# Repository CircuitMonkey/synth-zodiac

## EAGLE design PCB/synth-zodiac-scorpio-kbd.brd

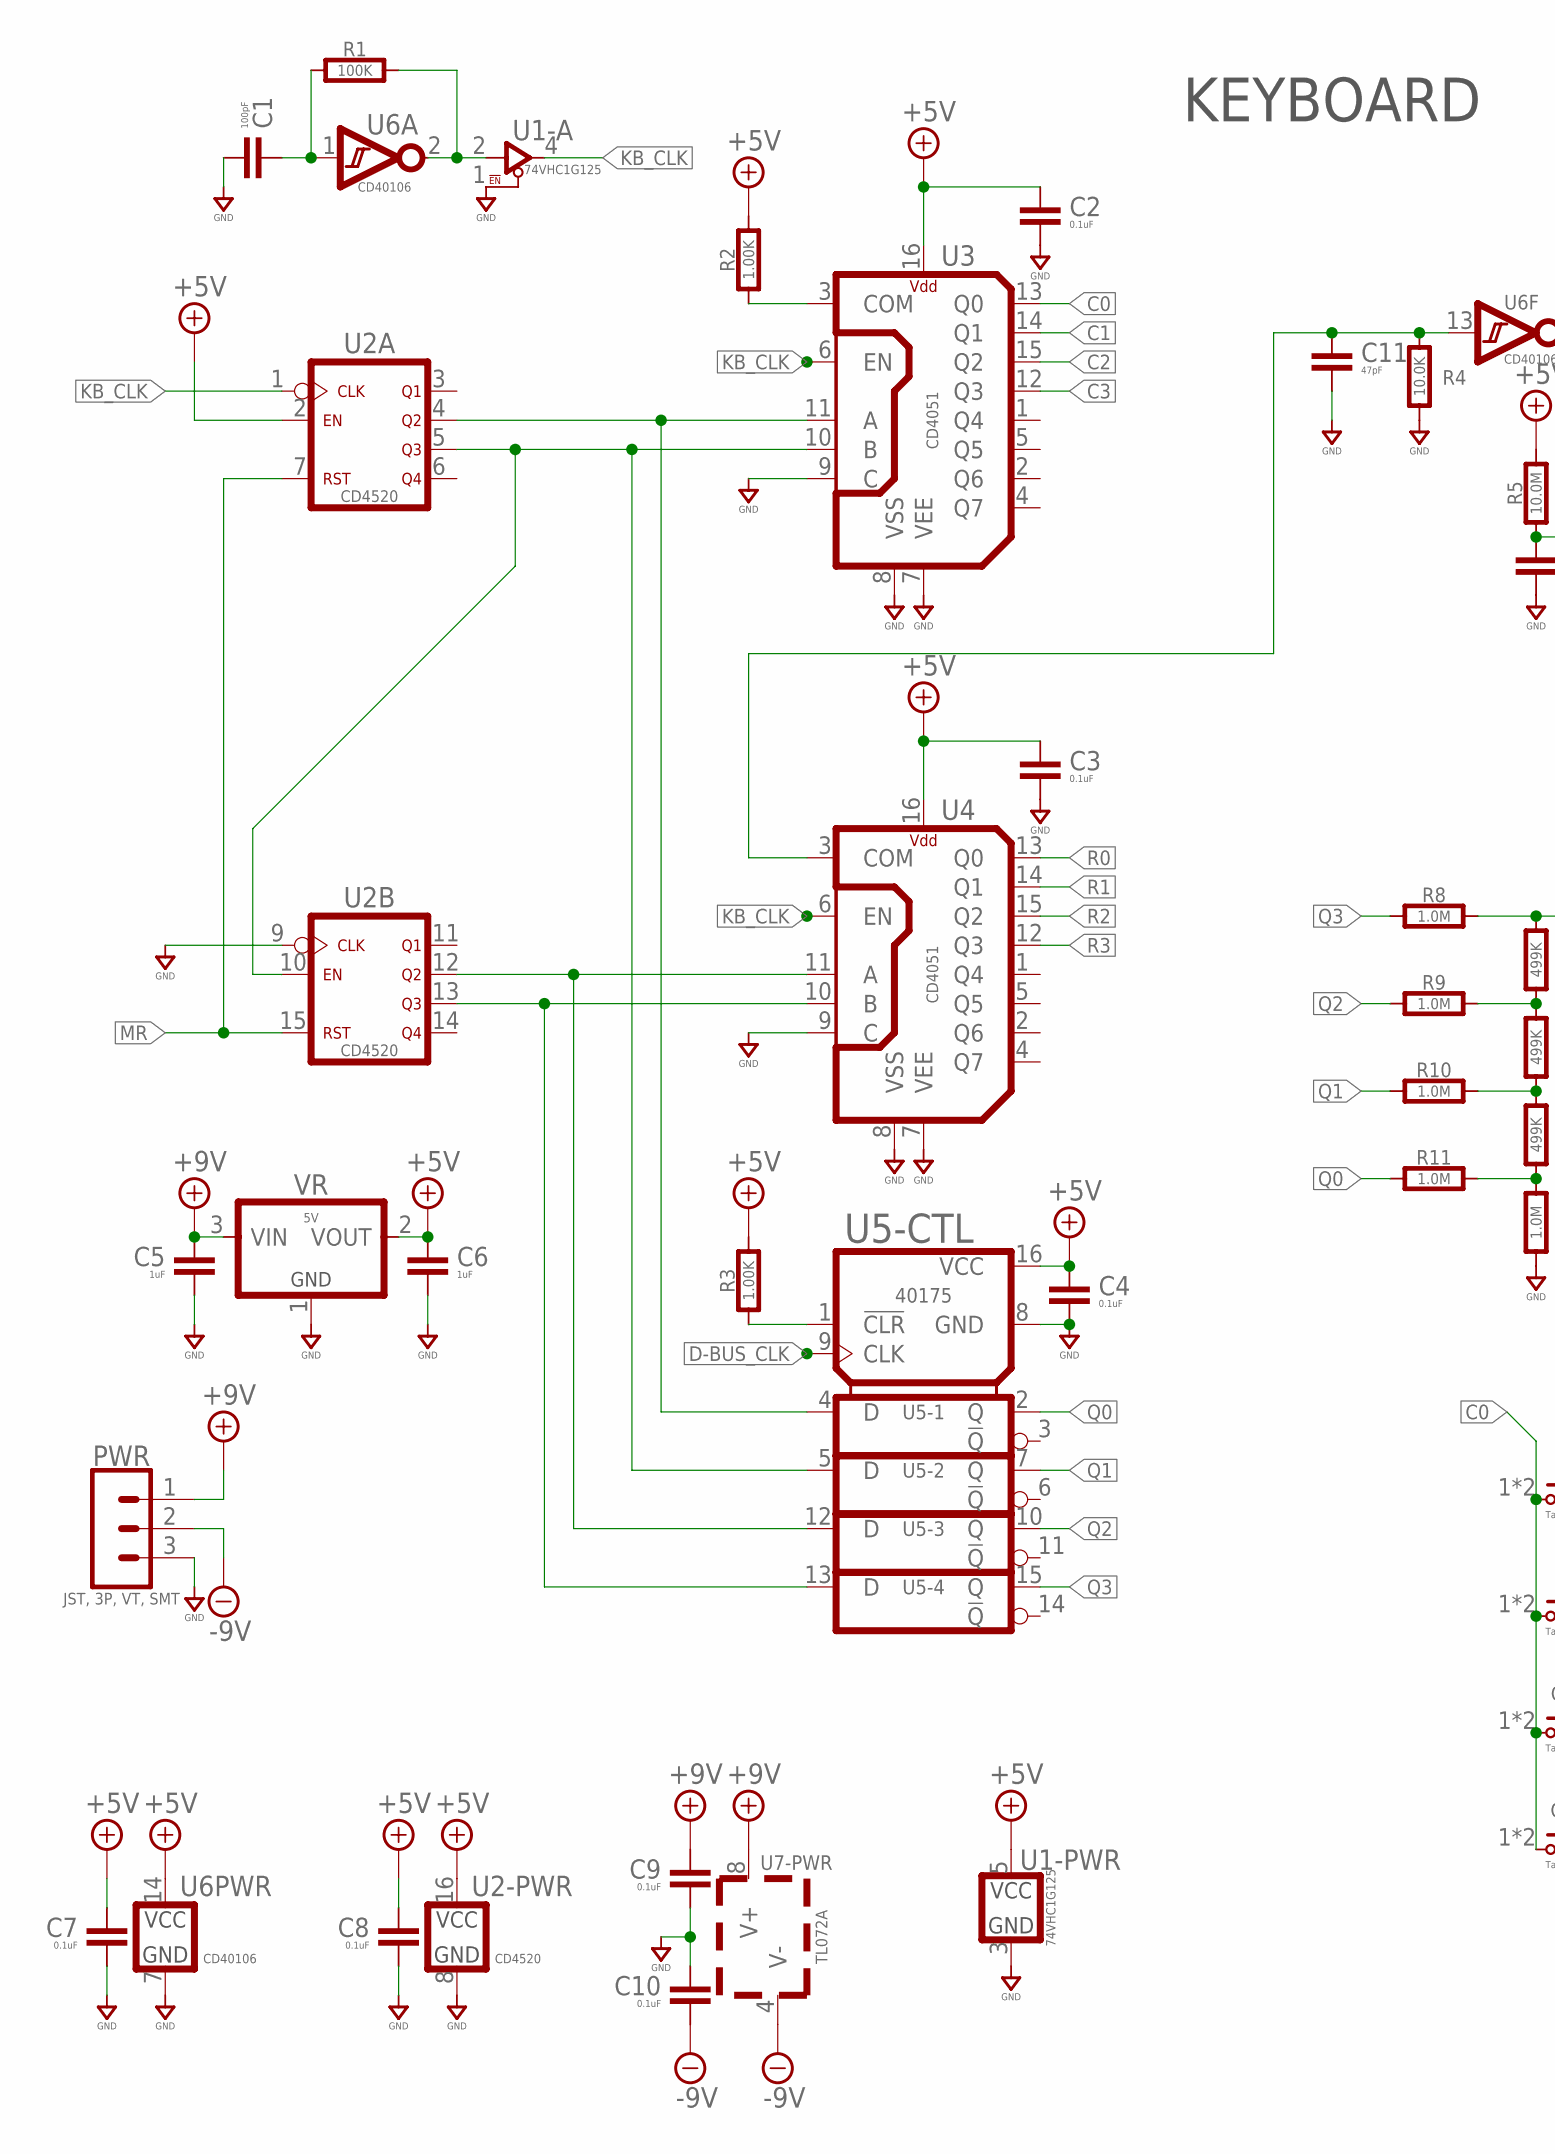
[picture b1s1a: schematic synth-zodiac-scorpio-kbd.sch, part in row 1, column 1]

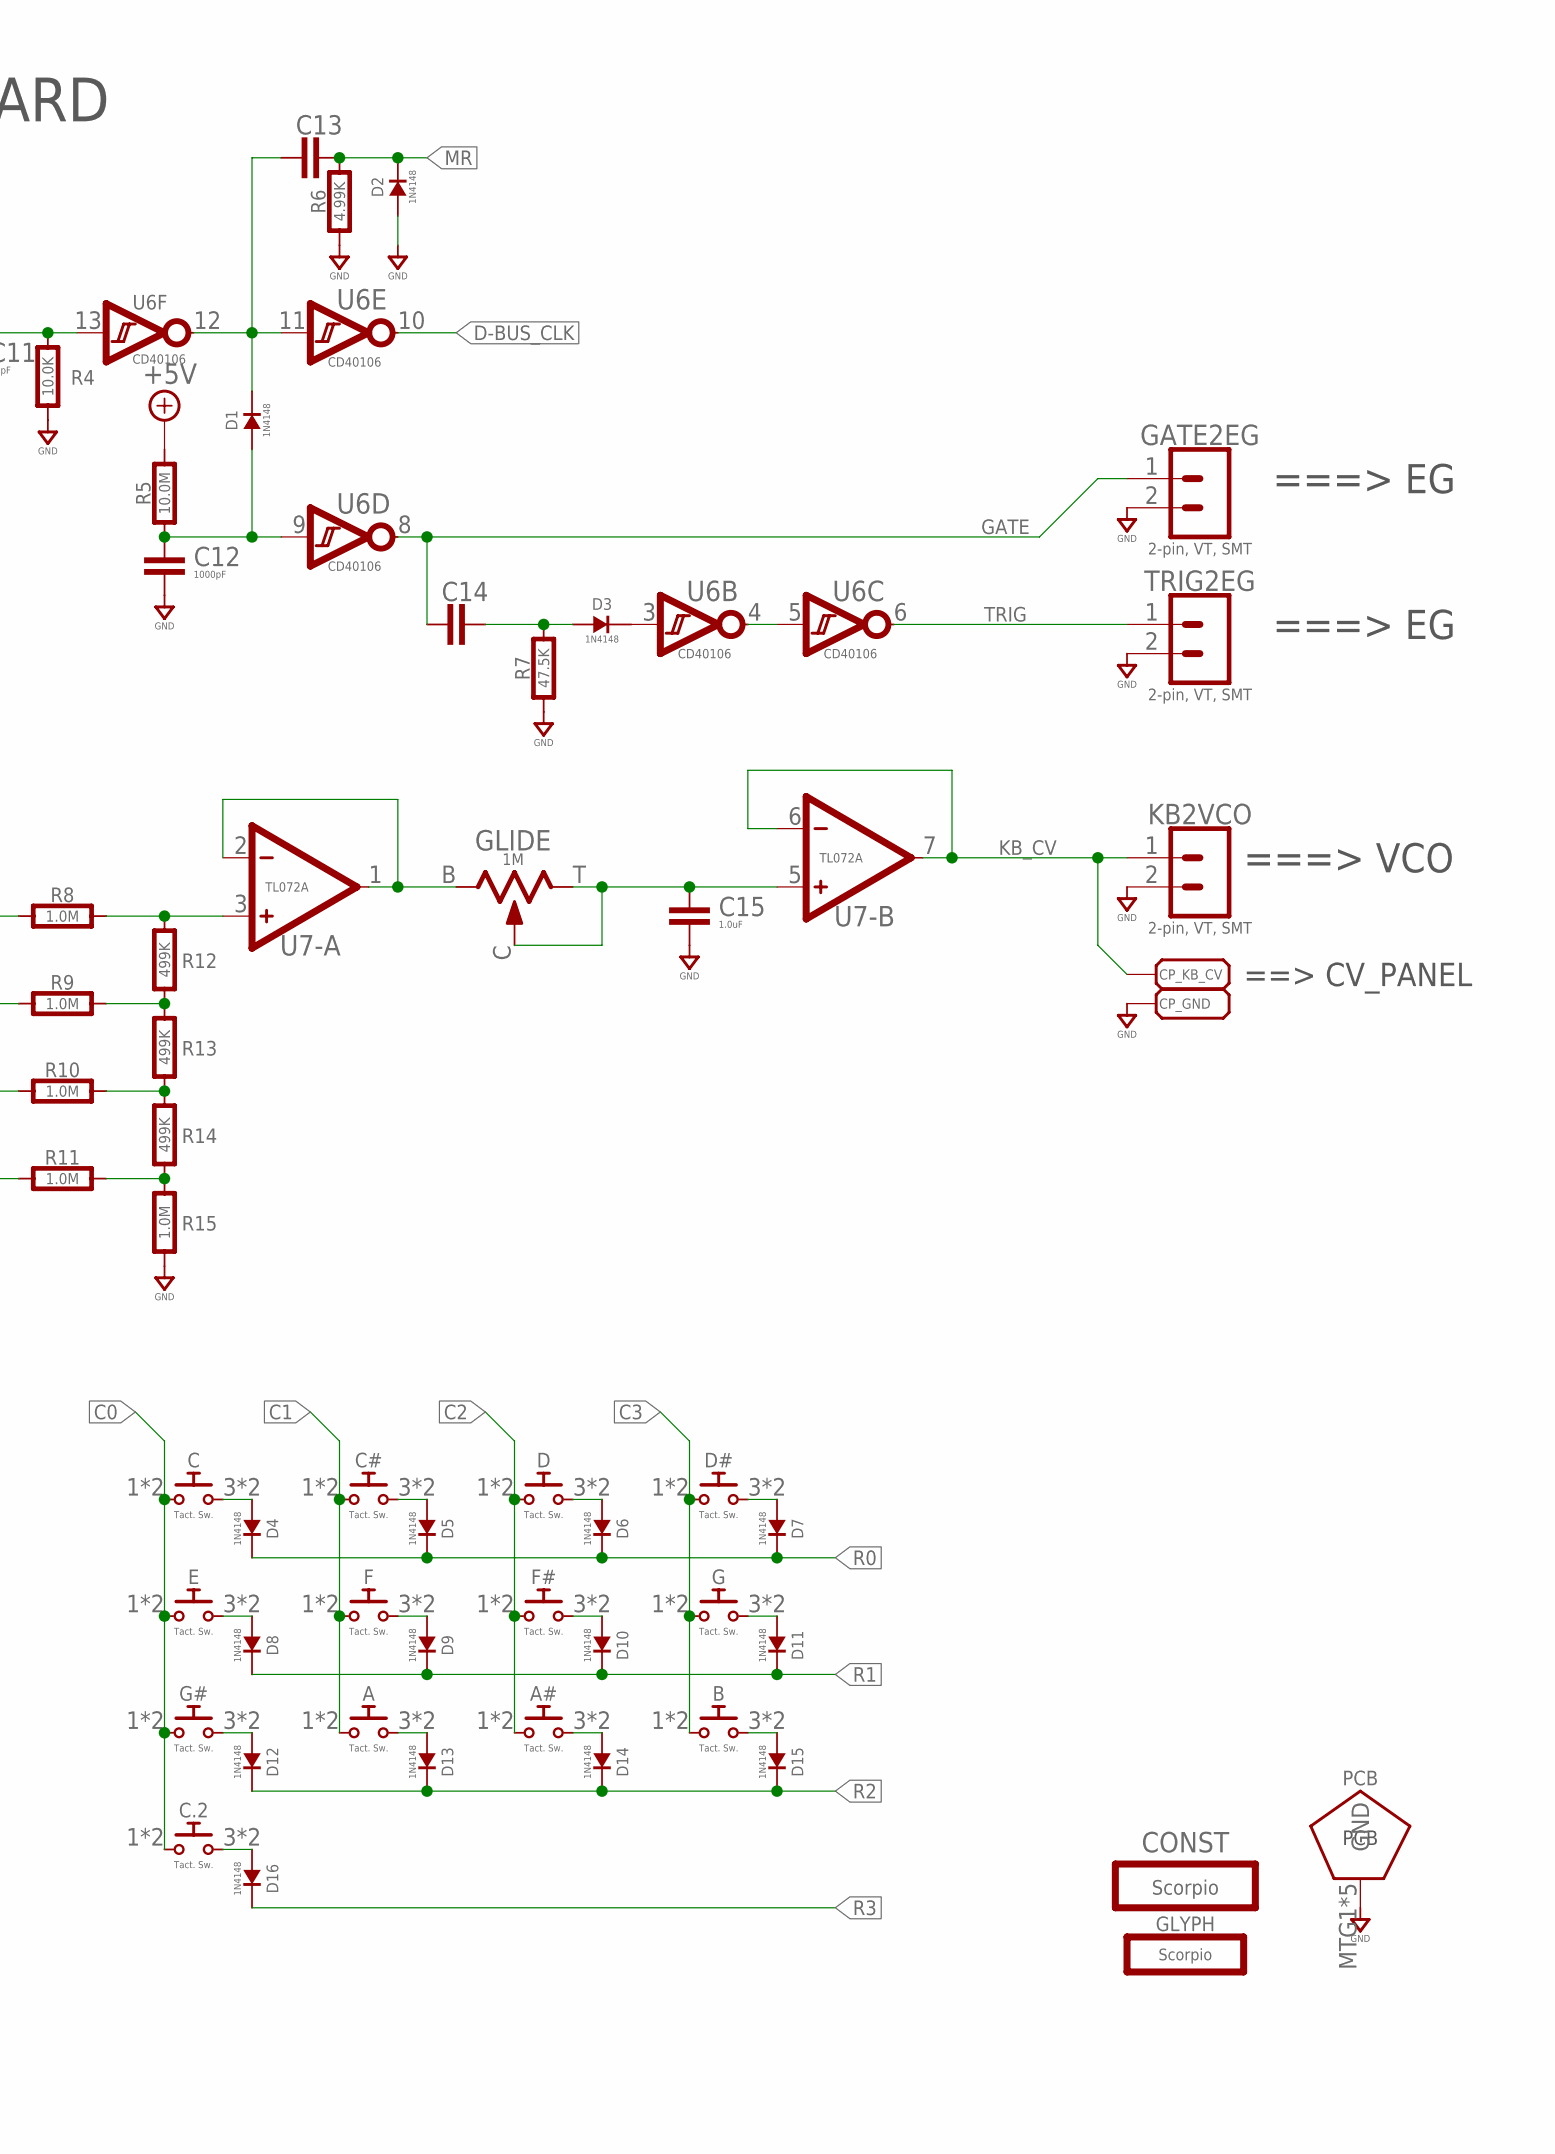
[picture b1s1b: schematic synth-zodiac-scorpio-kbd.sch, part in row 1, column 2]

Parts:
A: Tact. Sw.; B3FS
A#: Tact. Sw.; B3FS
B: Tact. Sw.; B3FS
C, C.2: Tact. Sw.; B3FS
C1: 100pF; 0603-CAP
C2, C3, C4, C7, C8, C9, C10, C14: 0.1uF; 0603-CAP
C5, C6: 1uF; 0603-CAP
C11: 47pF; 0603-CAP
C12: 1000pF; 0603-CAP
C13: 220pF; 0603-CAP
C15: 1.0uF; 0603-CAP
C#: Tact. Sw.; B3FS
CONST: Scorpio; SCORPIO-CONST
CP_GND: PAD-70X70SMD-070X070; SMD-070MIL
CP_KB_CV: PAD-70X70SMD-070X070; SMD-070MIL
D: Tact. Sw.; B3FS
D1, D2, D3, D4, D5, D6, D7, D8, D9, D10, D11, D12, D13, D14, D15, D16: 1N4148; SOD-123
D#: Tact. Sw.; B3FS
E: Tact. Sw.; B3FS
F: Tact. Sw.; B3FS
F#: Tact. Sw.; B3FS
G: Tact. Sw.; B3FS
G#: Tact. Sw.; B3FS
GATE2EG: 2-pin, VT, SMT; B2B-PH-SM4
GLIDE: 1M; POT-RV9110
GLYPH: Scorpio; SCORPIO-GLYPH
KB2VCO: 2-pin, VT, SMT; B2B-PH-SM4
PCB: PCB FAB; PENTAGON-40MM-RAD
PWR: JST, 3P, VT, SMT; B3B-PH-SM4
R1: 100K; 0603-RES
R2, R3: 1.00K; 0603-RES
R4: 10.0K; 0603-RES
R5: 10.0M; 0603-RES
R6: 4.99K; 0603-RES
R7: 47.5K; 0603-RES
R8, R9, R10, R11, R15: 1.0M; 0603-RES
R12, R13, R14: 499K; 0603-RES
TRIG2EG: 2-pin, VT, SMT; B2B-PH-SM4
U1: 74VHC1G125; TSOP-5
U2: CD4520; SO16
U3, U4: CD4051; SO16
U5: 40175; SO16
U6: CD40106; SOP14
U7: TL072A; SOP08
VR: 5V; SOT-23

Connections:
+5V: C2.1, C3.1, C4.1, C6.1, C7.1, C8.1, R2.2, R3.2, R5.2, U1.5 (VCC), U2.2 (EN), U2.16 (VCC), U3.16 (VDD), U4.16 (VDD), U5.16 (VCC), U6.14 (VCC), VR.2 (VOUT)
+9V: C5.1, C9.1, PWR.1, U7.8 (V+), VR.3 (VIN)
-9V: C10.2, PWR.2, U7.4 (V-)
C0: C.1, C.2 (1), C.2.1, C.2.2 (1), E.1, E.2 (1), G#.1, G#.2 (1), U3.13 (Q0)
C1: A.1, A.2 (1), C#.1, C#.2 (1), F.1, F.2 (1), U3.14 (Q1)
C2: A#.1, A#.2 (1), D.1, D.2 (1), F#.1, F#.2 (1), U3.15 (Q2)
C3: B.1, B.2 (1), D#.1, D#.2 (1), G.1, G.2 (1), U3.12 (Q3)
D-BUS_CLK: U5.9 (CLK), U6.10 (Y)
GATE: C14.1, GATE2EG.1, U6.8 (Y)
GND: C1.2, C2.2, C3.2, C4.2, C5.2, C6.2, C7.2, C8.2, C9.2, C10.1, C11.2, C12.2, C15.2, CP_GND.1, D2.A, GATE2EG.2, KB2VCO.2, PCB.MTG1, PCB.MTG2, PCB.MTG3, PCB.MTG4, PCB.MTG5, PWR.3, R4.1, R6.1, R7.1, R15.1, TRIG2EG.2, U1.1 (!EN), U1.3 (GND), U2.8 (GND), U2.9 (!CLK), U3.7 (VEE), U3.8 (VSS), U3.9 (C), U4.7 (VEE), U4.8 (VSS), U4.9 (C), U5.8 (GND), U6.7 (GND), VR.1 (GND)
KB_CLK: U1.4 (Y), U2.1 (!CLK), U3.6 (EN), U4.6 (EN)
KB_CV: CP_KB_CV.1, KB2VCO.1, U7.6 (-), U7.7 (OUT)
MR: C13.2, D2.K, R6.2, U2.7 (RST), U2.15 (RST)
unnamed: R2.1, U3.3 (COM)
unnamed: C12.1, D1.A, R5.1, U6.9 (A)
unnamed: R3.1, U5.1 (!CLR)
unnamed: U6.4 (Y), U6.5 (A)
unnamed: U2.12 (Q2), U4.11 (A), U5.12 (D)
unnamed: U2.13 (Q3), U4.10 (B), U5.13 (D)
unnamed: C1.1, R1.1, U6.1 (A)
unnamed: R1.2, U1.2 (A), U6.2 (Y)
unnamed: U2.4 (Q2), U3.11 (A), U5.4 (D)
unnamed: U2.5 (Q3), U2.10 (EN), U3.10 (B), U5.5 (D)
unnamed: R11.2, R14.1, R15.2
unnamed: C13.1, D1.K, U6.11 (A), U6.12 (Y)
unnamed: R10.2, R13.1, R14.2
unnamed: D3.K, U6.3 (A)
unnamed: C14.2, D3.A, R7.2
unnamed: C11.1, R4.2, U4.3 (COM), U6.13 (A)
unnamed: R9.2, R12.1, R13.2
unnamed: R8.2, R12.2, U7.3 (+)
unnamed: GLIDE.B (1), U7.1 (OUT), U7.2 (-)
unnamed: C.3 (2), C.4 (2), D4.A
unnamed: C15.1, GLIDE.C (2), GLIDE.T (3), U7.5 (+)
unnamed: C#.3 (2), C#.4 (2), D5.A
unnamed: D.3 (2), D.4 (2), D6.A
unnamed: D7.A, D#.3 (2), D#.4 (2)
unnamed: D8.A, E.3 (2), E.4 (2)
unnamed: D9.A, F.3 (2), F.4 (2)
unnamed: D10.A, F#.3 (2), F#.4 (2)
unnamed: D11.A, G.3 (2), G.4 (2)
unnamed: D12.A, G#.3 (2), G#.4 (2)
unnamed: A.3 (2), A.4 (2), D13.A
unnamed: A#.3 (2), A#.4 (2), D14.A
unnamed: B.3 (2), B.4 (2), D15.A
unnamed: C.2.3 (2), C.2.4 (2), D16.A
Q0: R11.1, U5.2 (Q)
Q1: R10.1, U5.7 (Q)
Q2: R9.1, U5.10 (Q)
Q3: R8.1, U5.15 (Q)
R0: D4.K, D5.K, D6.K, D7.K, U4.13 (Q0)
R1: D8.K, D9.K, D10.K, D11.K, U4.14 (Q1)
R2: D12.K, D13.K, D14.K, D15.K, U4.15 (Q2)
R3: D16.K, U4.12 (Q3)
TRIG: TRIG2EG.1, U6.6 (Y)

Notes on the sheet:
KEYBOARD
===> EG
===> VCO
==> CV_PANEL

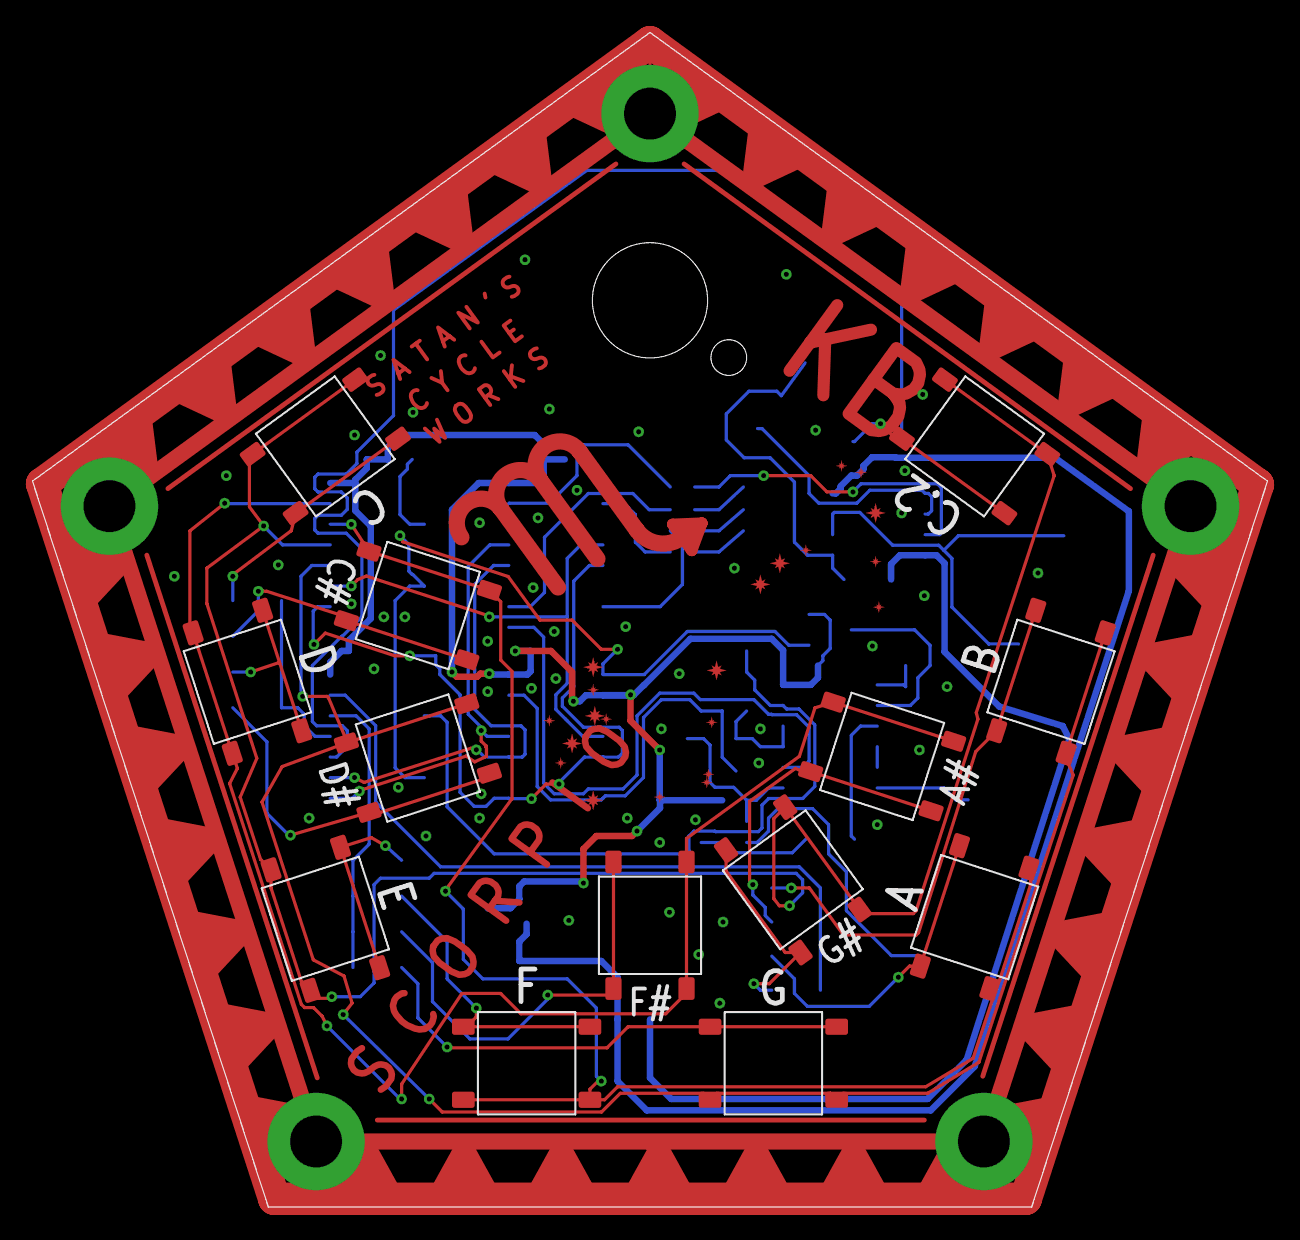
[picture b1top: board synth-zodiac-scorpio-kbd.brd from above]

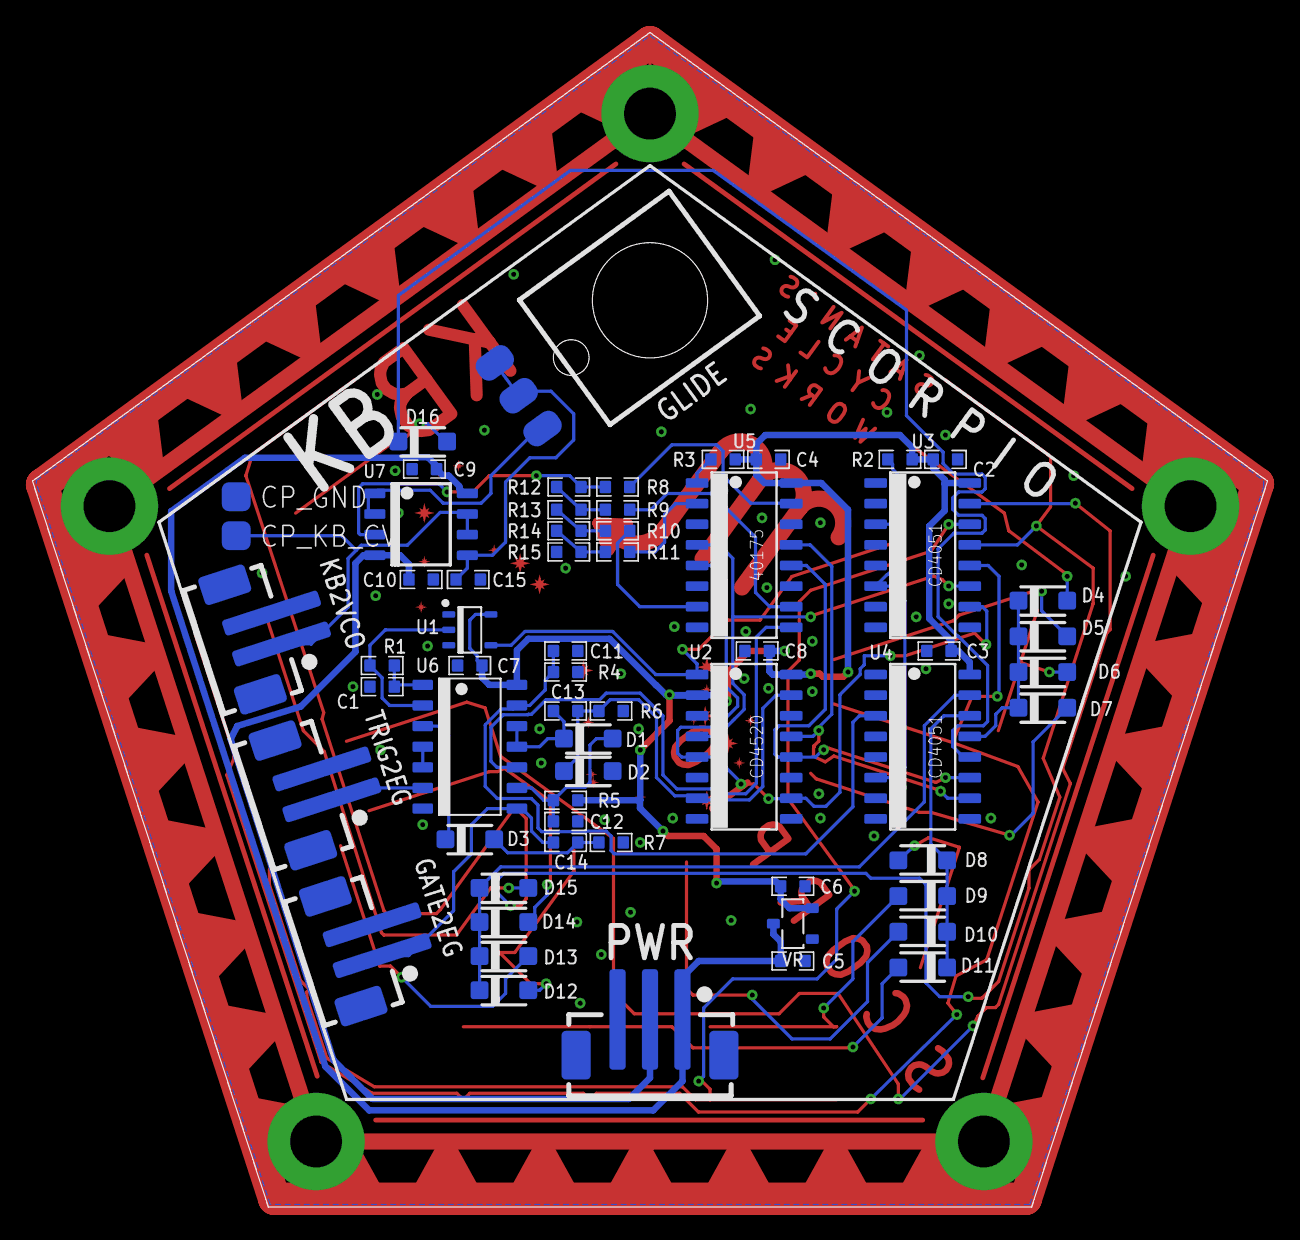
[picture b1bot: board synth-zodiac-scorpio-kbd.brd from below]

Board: 2 copper layers, 76.1 x 72.4 mm, 77 parts (61 on the bottom side), 55 nets.

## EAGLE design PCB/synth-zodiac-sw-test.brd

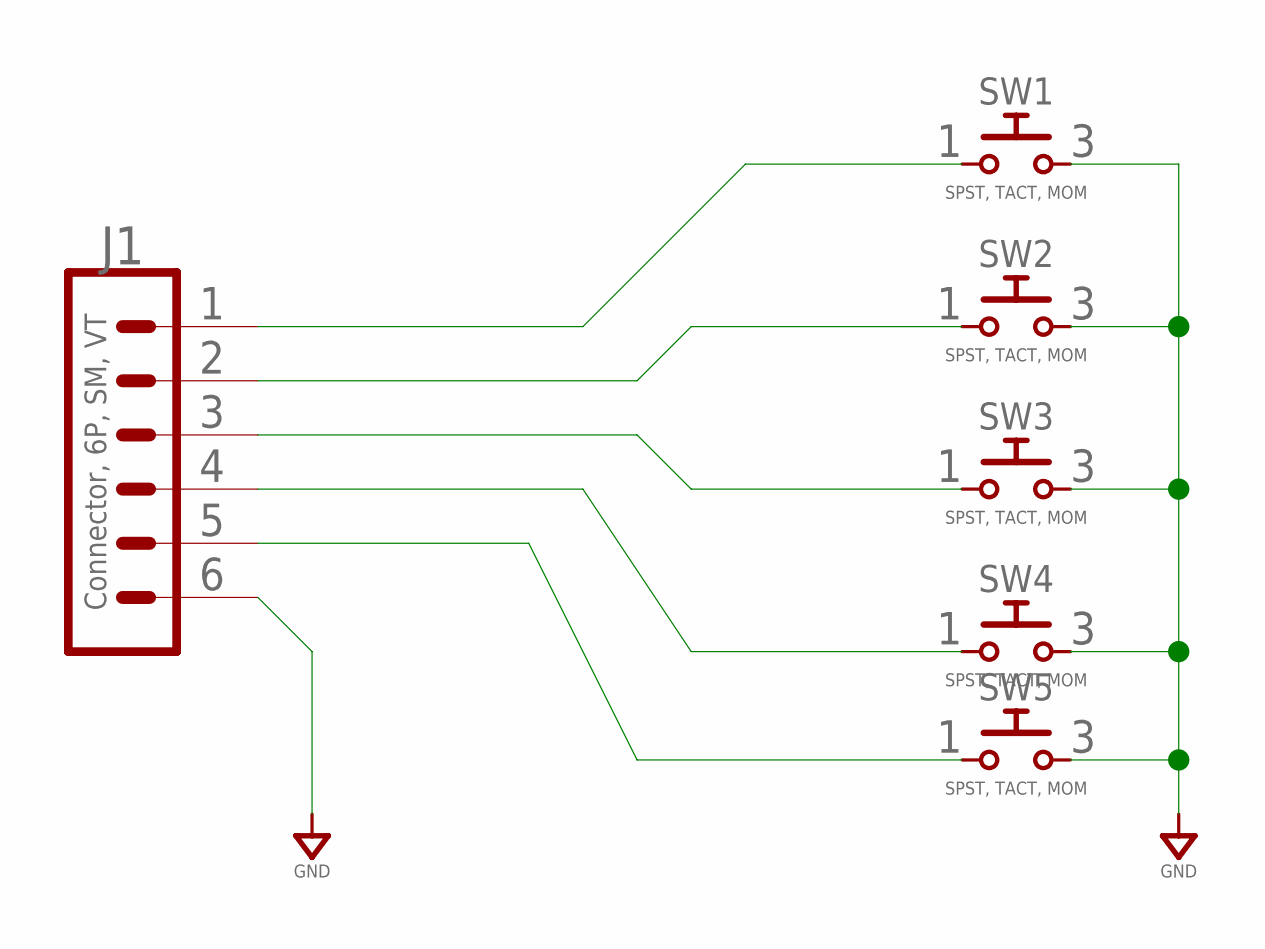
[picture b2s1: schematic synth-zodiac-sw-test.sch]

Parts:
J1: Connector, 6P, SM, VT; BM06B-SRSS-TB
SW1, SW2, SW3, SW4, SW5: SPST, TACT, MOM; B3FS-BACKMOUNT

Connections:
GND: J1.6, SW1.3 (2), SW2.3 (2), SW3.3 (2), SW4.3 (2), SW5.3 (2)
unnamed: J1.5, SW5.1
unnamed: J1.4, SW4.1
unnamed: J1.3, SW3.1
unnamed: J1.2, SW2.1
unnamed: J1.1, SW1.1

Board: 2 copper layers, 6 parts (1 on the bottom side), 6 nets.
